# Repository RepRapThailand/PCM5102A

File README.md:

# PCM5102A
PCM5102A - I2S DAC

JP2 = 3.3v LDO Select

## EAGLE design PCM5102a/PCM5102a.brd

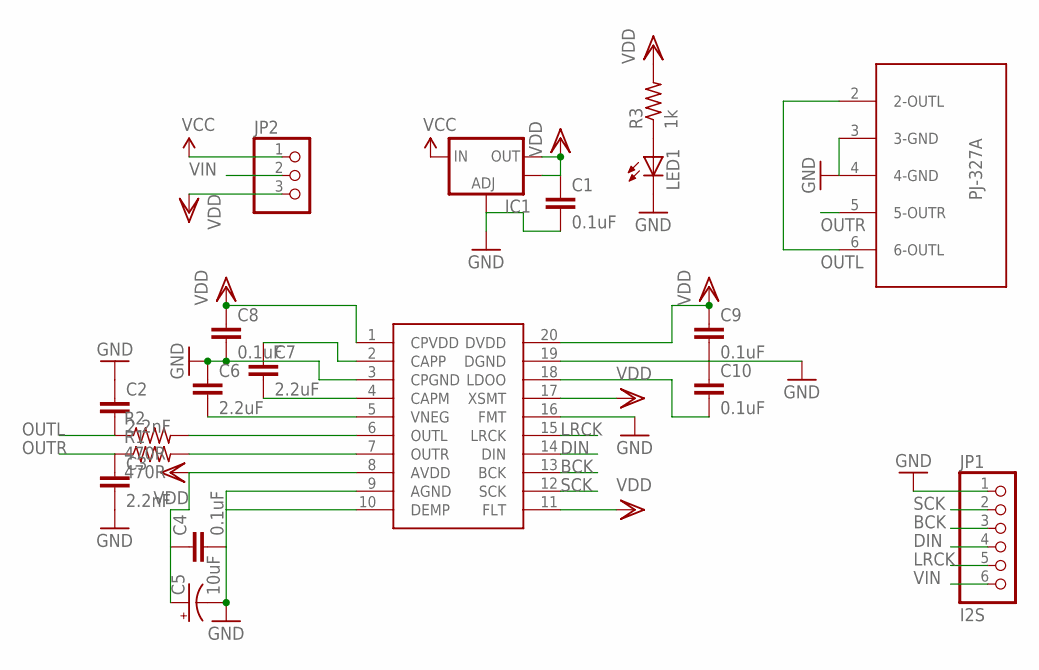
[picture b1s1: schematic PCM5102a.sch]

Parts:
C1, C4, C8, C9, C10: 0.1uF; 1206
C2, C3: 2.2nF; C5B2.5
C5: 10uF; NIPPON_F80
C6, C7: 2.2uF; 1206
IC1: V_REG_LM1117SOT223; SOT223
JP1: I2S; 1X06/90
JP2: PINHD-1X3; 1X03
LED1: LEDCHIP-LED0805; CHIP-LED0805
R1, R2: 470R; 0207/10
R3: 1k; 0207/10
U$1: PCM5102; TSSOP20
U$2: PJ-327A

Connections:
BCK: JP1.3, U$1.13 (BCK)
DIN: JP1.4, U$1.14 (DIN)
GND: C1.2, C2.1, C3.2, C4.2, C5.-, C6.1, C8.2, C9.2, C10.1, IC1.1 (ADJ), JP1.1, LED1.C, U$1.3 (CPGND), U$1.9 (AGND), U$1.10 (DEMP), U$1.16 (FMT), U$1.19 (DGND), U$2.3 (3-GND), U$2.4 (4-GND)
LRCK: JP1.5, U$1.15 (LRCK)
unnamed: C7.1, U$1.2 (CAPP)
unnamed: C7.2, U$1.4 (CAPM)
unnamed: R1.2, U$1.7 (OUTR)
unnamed: R2.2, U$1.6 (OUTL)
unnamed: C6.2, U$1.5 (VNEG)
unnamed: C10.2, U$1.18 (LDOO)
unnamed: LED1.A, R3.1
OUTL: C2.2, R2.1, U$2.2 (2-OUTL), U$2.6 (6-OUTL)
OUTR: C3.1, R1.1, U$2.5 (5-OUTR)
SCK: JP1.2, U$1.12 (SCK)
VCC: IC1.3 (IN), JP2.1
VDD: C1.1, C4.1, C5.+, C8.1, C9.1, IC1.2 (OUT), IC1.4 (OUT), JP2.3, R3.2, U$1.1 (CPVDD), U$1.8 (AVDD), U$1.11 (FLT), U$1.17 (XSMT), U$1.20 (DVDD)
VIN: JP1.6, JP2.2

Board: 2 copper layers, 19 parts (1 on the bottom side), 17 nets, no tracks yet.

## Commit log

2015-04-28 PCM5102A ver1.0.0

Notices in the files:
parts and their libraries:
SparkFun-PowerIC: Licensing: CC v3.0 Share-Alike You are welcome to use this library for commercial purposes.
